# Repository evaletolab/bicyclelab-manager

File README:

# bicyclelab.ORG

Take the control of your electric bicycle. Manage the energy consumtion, wireless I/O with RFM12 or bluetooth, the display, the throttle, the charging, every pieces are open source.

**THIS IS ALPHA SOFTWARE/HARDWARE AND SHOULD BE TREATED ACCORDINGLY.**
**IT IS FUN TO GET RUNNING, BUT EXPECT THINGS TO BE BROKEN.**

##Roadmap
This is a long term project, here is the list of the first ideas: 
* Manage/control your electric bicycle kit with our lithium/electronics/software replacement
* Log data, power, battery voltage, throttle, 
* Use RFM12b as throttle and battery display
* Develop an android application 
* Create the li-ion battery protection module   
* Use the battery for other target with DC 5V 3A output

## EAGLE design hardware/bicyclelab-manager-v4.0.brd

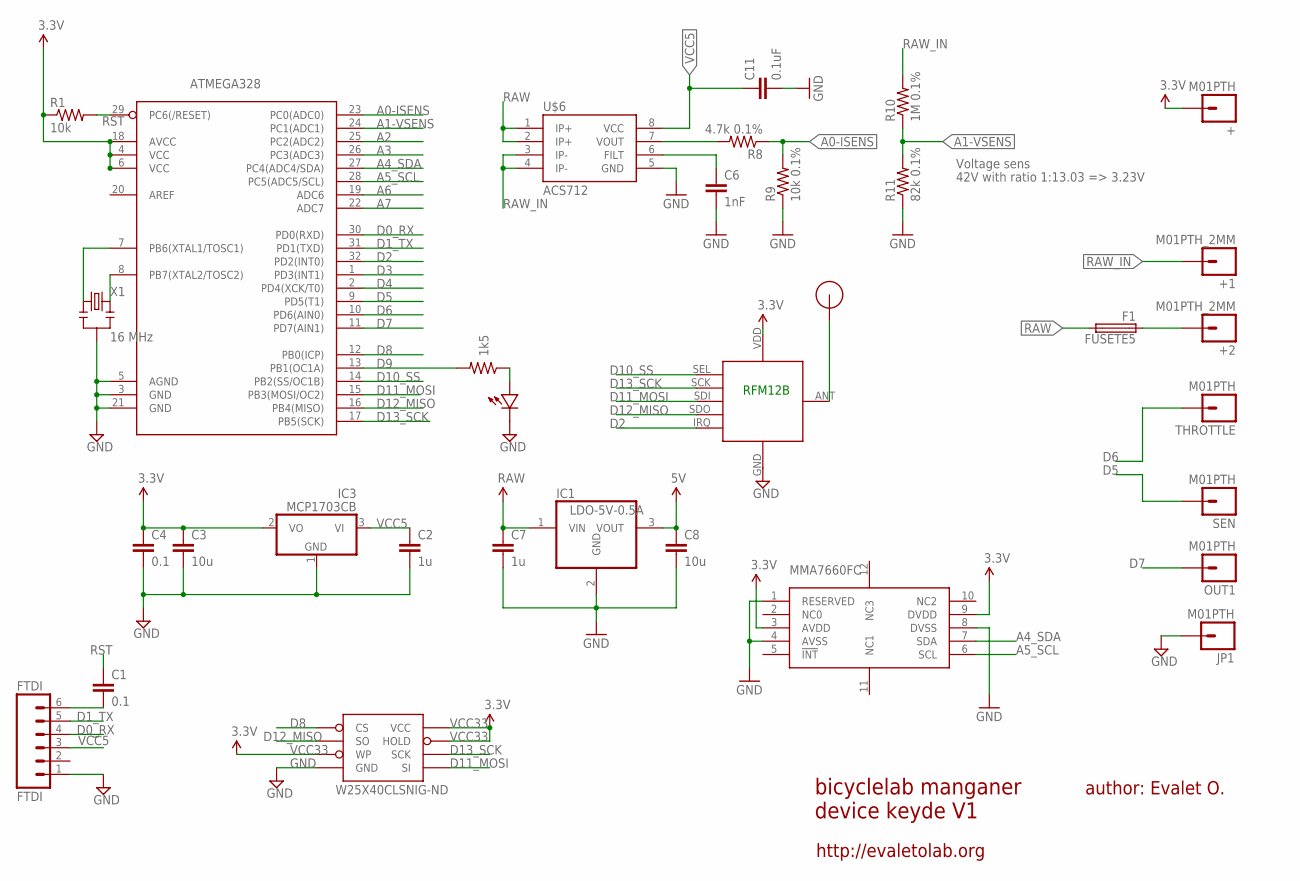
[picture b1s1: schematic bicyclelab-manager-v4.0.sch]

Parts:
+: M01PTH; 1X01
+1, +2: M01PTH_2MM; 1X01_2MM
ATMEGA328: ATMega-328; TQFP32-08
C1, C4: 0.1; 0603-CAP
C2, C7: 1u; 0603-CAP
C3, C8: 10u; 0805-CAP
C6: 1nF; 0805
C11: 0.1uF; 0805
F1: FUSETE5; TE5
FTDI: FTDI; 1X06
IC1: LDO-5V-0.5A; SOT223
IC3: MCP1703CB; SOT23
JP1: M01PTH; 1X01
MMA7660FC: MMA7660FC-DFN10; DFN10
OUT1: M01PTH; 1X01
R1: 10k; 0603-RES
R2: 1k5; 0603-RES
R8: 4.7k 0.1%; 0805
R9: 10k 0.1%; 0805
R10: 1M 0.1%; 0805
R11: 82k 0.1%; 0805
RFM12B: RFM12B_MINPADS; RFM12B-MINPADS
SEN: M01PTH; 1X01
THROTTLE: M01PTH; 1X01
U$1: RFM12B_ANTENNA; RFM12B-ANTENNA
U$2: LED0603; 0603-LED
U$6: ACS712; SO08
W25X40CLSNIG-ND: AT25F512BWIDE_5.3MM; SO08WIDE
X1: 16 MHz; RESONATOR-SMD

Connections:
A0-ISENS: ATMEGA328.23 (PC0(ADC0)), R8.1, R9.2
A1-VSENS: ATMEGA328.24 (PC1(ADC1)), R10.1, R11.2
A2: ATMEGA328.25 (PC2(ADC2))
A3: ATMEGA328.26 (PC3(ADC3))
A4_SDA: ATMEGA328.27 (PC4(ADC4/SDA)), MMA7660FC.7 (SDA)
A5_SCL: ATMEGA328.28 (PC5(ADC5/SCL)), MMA7660FC.6 (SCL)
A6: ATMEGA328.19 (ADC6)
A7: ATMEGA328.22 (ADC7)
D0_RX: ATMEGA328.30 (PD0(RXD)), FTDI.4
D1_TX: ATMEGA328.31 (PD1(TXD)), FTDI.5
D2: ATMEGA328.32 (PD2(INT0)), RFM12B.IRQ
D3: ATMEGA328.1 (PD3(INT1))
D4: ATMEGA328.2 (PD4(XCK/T0))
D5: ATMEGA328.9 (PD5(T1)), SEN.1
D6: ATMEGA328.10 (PD6(AIN0)), THROTTLE.1
D7: ATMEGA328.11 (PD7(AIN1)), OUT1.1
D8: ATMEGA328.12 (PB0(ICP)), W25X40CLSNIG-ND.1 (CS)
D9: ATMEGA328.13 (PB1(OC1A)), R2.2
D10_SS: ATMEGA328.14 (PB2(SS/OC1B)), RFM12B.SEL
D11_MOSI: ATMEGA328.15 (PB3(MOSI/OC2)), RFM12B.SDI (SDI/MOSI), W25X40CLSNIG-ND.5 (SI)
D12_MISO: ATMEGA328.16 (PB4(MISO)), RFM12B.SDO (SDO/MISO), W25X40CLSNIG-ND.2 (SO)
D13_SCK: ATMEGA328.17 (PB5(SCK)), RFM12B.SCK, W25X40CLSNIG-ND.6 (SCK)
GND: ATMEGA328.3 (GND), ATMEGA328.5 (AGND), ATMEGA328.21 (GND), C2.2, C3.2, C4.2, C6.2, C7.2, C8.2, C11.2, FTDI.1, IC1.2 (GND), IC3.1 (GND), JP1.1, MMA7660FC.1 (RESERVED), MMA7660FC.4 (AVSS), MMA7660FC.8 (DVSS), R9.1, R11.1, RFM12B.GND, U$2.MINUS, U$6.5 (GND), W25X40CLSNIG-ND.4 (GND), X1.2
IOUT_: R8.2, U$6.7 (VOUT)
unnamed: ATMEGA328.7 (PB6(XTAL1/TOSC1)), X1.1
unnamed: R2.1, U$2.PLUS
unnamed: RFM12B.ANT, U$1.P$1
unnamed: C6.1, U$6.6 (FILT)
unnamed: C1.2, FTDI.6
unnamed: ATMEGA328.8 (PB7(XTAL2/TOSC2)), X1.3
RAW: C7.1, F1.2, IC1.1 (VIN), U$6.1 (IP+), U$6.2 (IP+)
RAW_IN: +1.1, R10.2, U$6.3 (IP-), U$6.4 (IP-)
RAW_OUT: +2.1, F1.1
RST: ATMEGA328.29 (PC6(/RESET)), C1.1, R1.2
VCC5: C2.1, C8.1, C11.1, FTDI.3, IC1.3 (VOUT), IC3.3 (VI), U$6.8 (VCC)
VCC33: +.1, ATMEGA328.4 (VCC), ATMEGA328.6 (VCC), ATMEGA328.18 (AVCC), C3.1, C4.1, IC3.2 (VO), MMA7660FC.3 (AVDD), MMA7660FC.9 (DVDD), R1.1, RFM12B.VDD, W25X40CLSNIG-ND.3 (WP), W25X40CLSNIG-ND.7 (HOLD), W25X40CLSNIG-ND.8 (VCC)

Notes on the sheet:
bicyclelab manganer device keyde V1
author: Evalet O.
http://evaletolab.org
RFM12B
42V with ratio 1:13.03 => 3.23V
Voltage sens

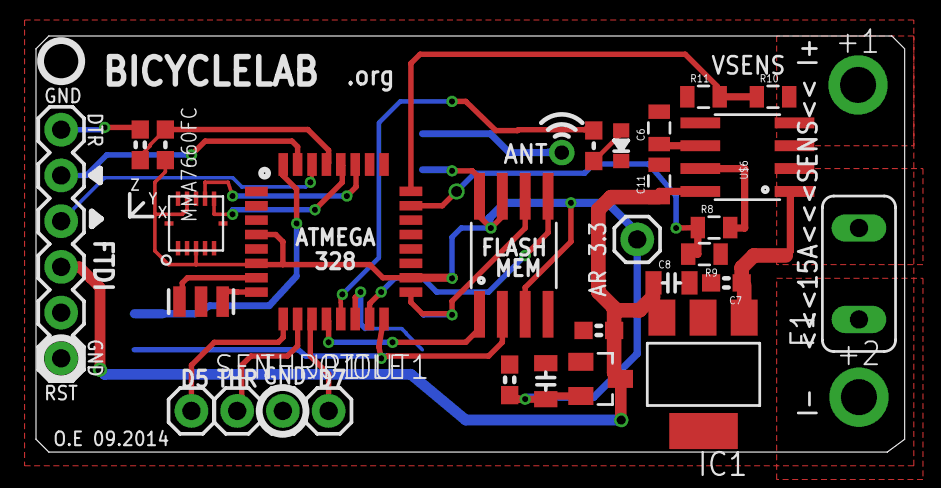
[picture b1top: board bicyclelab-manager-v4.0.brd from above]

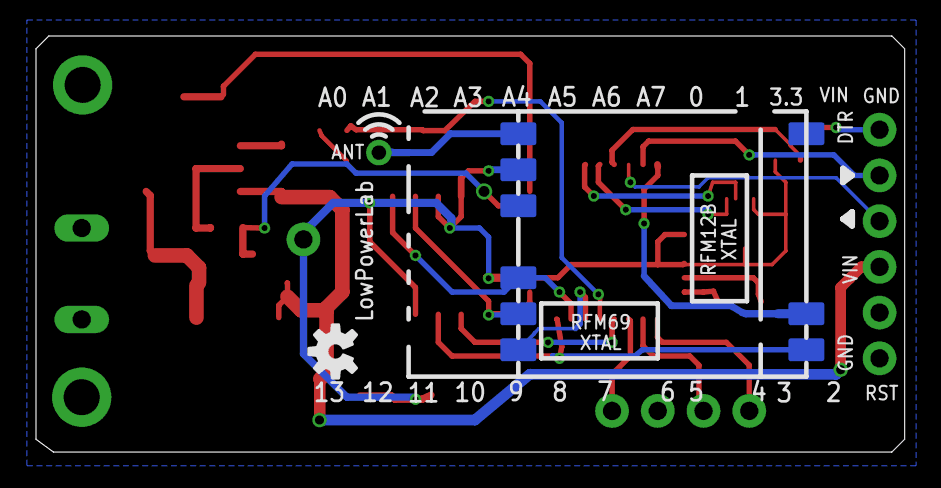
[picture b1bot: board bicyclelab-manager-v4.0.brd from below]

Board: 2 copper layers, 48.3 x 23.1 mm, 34 parts (2 on the bottom side), 30 nets.

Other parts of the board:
U$3: OSHW-LOGO-S

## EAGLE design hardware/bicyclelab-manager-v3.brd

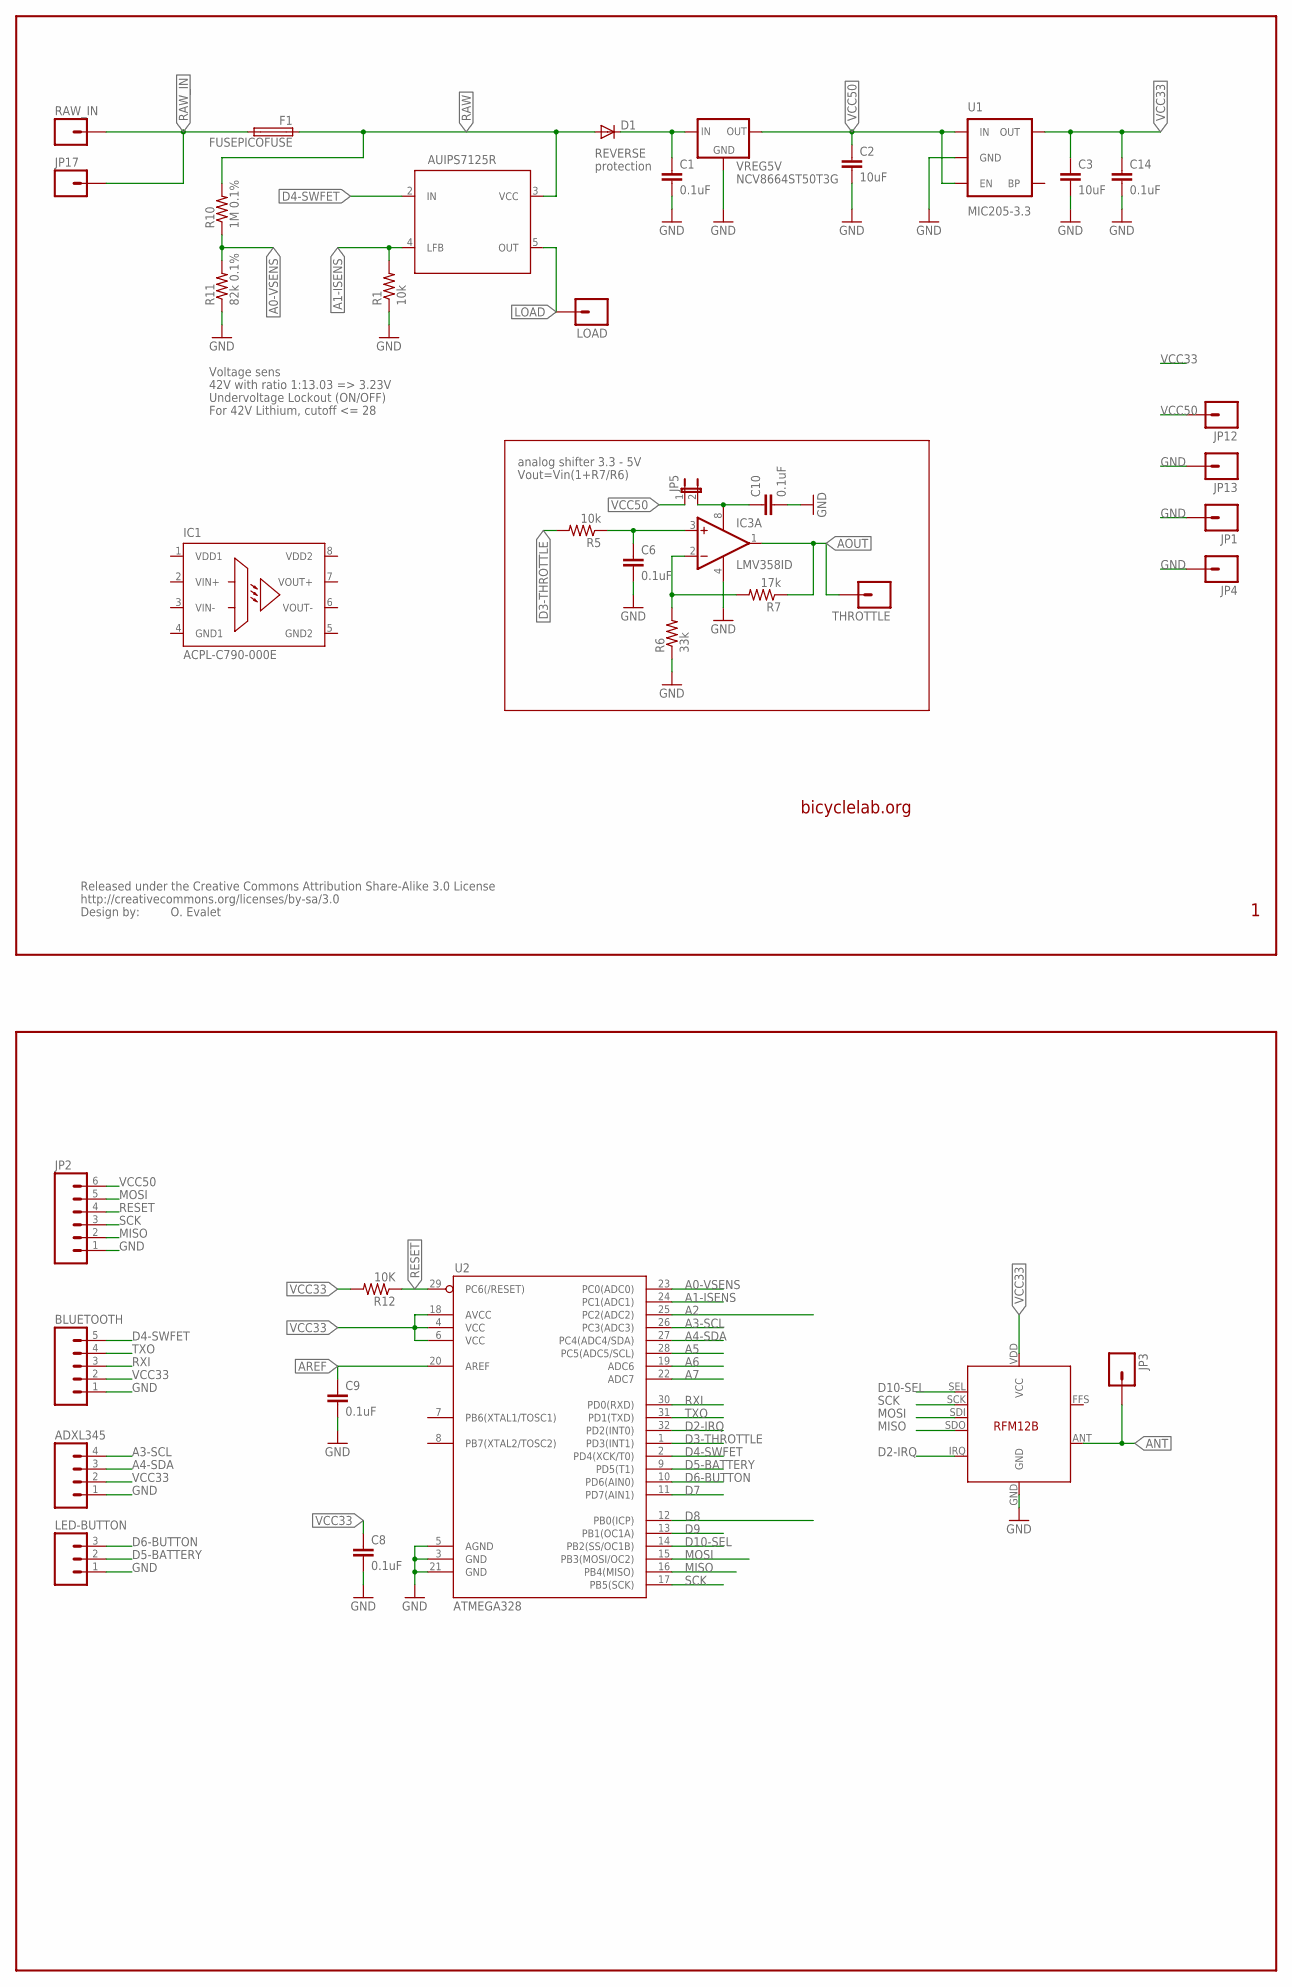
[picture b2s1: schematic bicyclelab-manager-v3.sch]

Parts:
ADXL345: M04PTH; 1X04
BLUETOOTH: M05PTH; 1X05
C1, C6, C10: 0.1uF; 0805
C2, C3: 10uF; 0805
C8, C9, C14: 0.1uF; 0603-CAP
D1: DIODESOD; SOD-323
F1: FUSEPICOFUSE; PICOFUSE
IC1: ACPL-C790-000E; DIP8
IC3: LMV358ID; SO08
JP1, JP4, JP17: M01PTH_2MM; 1X01_2MM
JP2: M06EM406; EM406
JP3: M01SMD-4.5X1.5; PAD-1.5X4.5
JP5: JUMPER-2PTH_LOCK; 1X02_LOCK
JP12, JP13: M01PTH; 1X01
LED-BUTTON: M03PTH; 1X03
LOAD: M01PTH_2MM; 1X01_2MM
R1, R5: 10k; 0805
R6: 33k; 0805
R7: 17k; 0805
R10: 1M 0.1%; 0805
R11: 82k 0.1%; 0805
R12: 10K; 0603-RES
RAW_IN: M01PTH_2MM; 1X01_2MM
THROTTLE: M01PTH; 1X01
U1: MIC205-3.3; SOT23-5
U2: ATMEGA328; TQFP32-08
U$1: RFM12B
U$5: CREATIVE_COMMONS
U$8: AUIPS7125R; DPAK-5
VREG5V: NCV8664ST50T3G; SOT223

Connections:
A0-VSENS: R10.1, R11.2, U2.23 (PC0(ADC0))
A1-ISENS: R1.2, U2.24 (PC1(ADC1)), U$8.4 (LFB)
A2: U2.25 (PC2(ADC2))
A3-SCL: ADXL345.4, U2.26 (PC3(ADC3))
A4-SDA: ADXL345.3, U2.27 (PC4(ADC4/SDA))
A5: U2.28 (PC5(ADC5/SCL))
A6: U2.19 (ADC6)
A7: U2.22 (ADC7)
ANT: JP3.P$1, U$1.ANT
AOUT: IC3.1 (OUT), R7.1, THROTTLE.1
AREF: C9.1, U2.20 (AREF)
D2-IRQ: U2.32 (PD2(INT0)), U$1.IRQ
D3-THROTTLE: R5.2, U2.1 (PD3(INT1))
D4-SWFET: BLUETOOTH.5, U2.2 (PD4(XCK/T0)), U$8.2 (IN)
D5-BATTERY: LED-BUTTON.2, U2.9 (PD5(T1))
D6-BUTTON: LED-BUTTON.3, U2.10 (PD6(AIN0))
D7: U2.11 (PD7(AIN1))
D8: U2.12 (PB0(ICP))
D9: U2.13 (PB1(OC1A))
D10-SEL: U2.14 (PB2(SS/OC1B)), U$1.SEL
GND: ADXL345.1, BLUETOOTH.1, C1.2, C2.2, C3.2, C6.2, C8.2, C9.2, C10.2, C14.2, IC3.4 (V-), JP1.1, JP2.1, JP4.1, JP13.1, LED-BUTTON.1, R1.1, R6.1, R11.1, U1.2 (GND), U2.3 (GND), U2.5 (AGND), U2.21 (GND), U$1.GND, VREG5V.2 (GND)
GND1: IC1.4 (GND1)
GND2: IC1.5 (GND2)
LOAD: LOAD.1, U$8.5 (OUT)
MISO: JP2.2, U2.16 (PB4(MISO)), U$1.SDO
MOSI: JP2.5, U2.15 (PB3(MOSI/OC2)), U$1.SDI
unnamed: C1.1, D1.1 (C), VREG5V.1 (IN)
unnamed: IC3.2 (-IN), R6.2, R7.2
unnamed: C6.1, IC3.3 (+IN), R5.1
RAW: D1.2 (A), F1.1, R10.2, U$8.3 (VCC)
RAW_IN: F1.2, JP17.1, RAW_IN.1
RESET: JP2.4, R12.1, U2.29 (PC6(/RESET))
RXI: BLUETOOTH.3, U2.30 (PD0(RXD))
SCK: JP2.3, U2.17 (PB5(SCK)), U$1.SCK
TXO: BLUETOOTH.4, U2.31 (PD1(TXD))
VCC33: ADXL345.2, BLUETOOTH.2, C3.1, C8.1, C14.1, R12.2, U1.5 (OUT), U2.4 (VCC), U2.6 (VCC), U2.18 (AVCC), U$1.VDD (VCC)
VCC50: C2.1, JP2.6, JP5.1, JP12.1, U1.1 (IN), U1.3 (EN), VREG5V.3 (OUT)
VCC50_: C10.1, IC3.8 (V+), JP5.2
VDD1: IC1.1 (VDD1)
VDD2: IC1.8 (VDD2)
VIN+: IC1.2 (VIN+)
VIN-: IC1.3 (VIN-)
VOUT+: IC1.7 (VOUT+)
VOUT-: IC1.6 (VOUT-)

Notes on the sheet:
bicyclelab.org
O. Evalet
Undervoltage Lockout (ON/OFF)
For 42V Lithium, cutoff <= 28
42V with ratio 1:13.03 => 3.23V
Voltage sens
analog shifter 3.3 - 5V
Vout=Vin(1+R7/R6)
REVERSE
protection

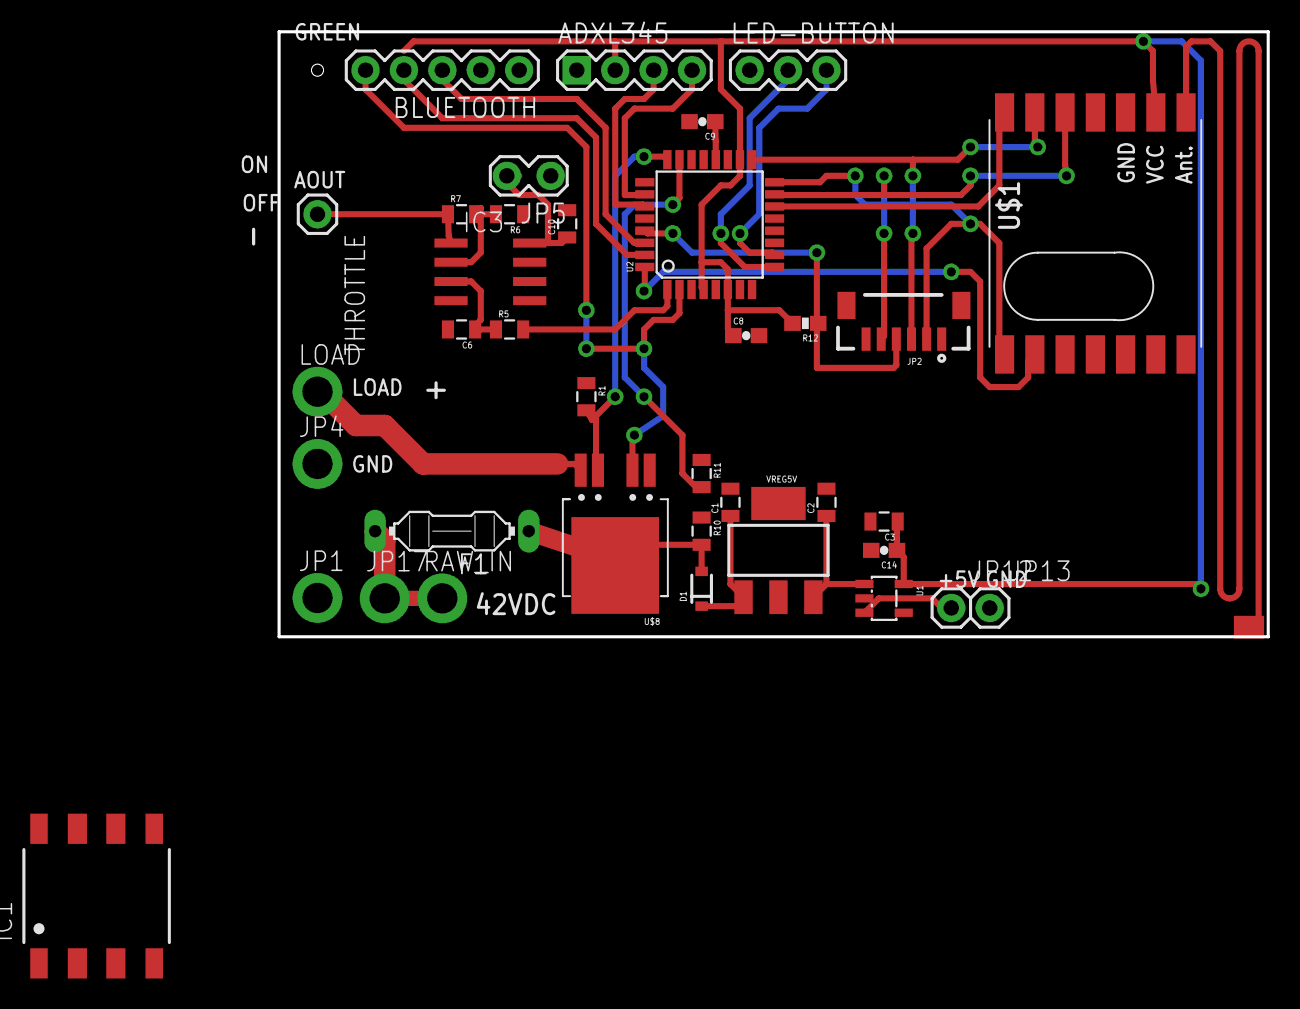
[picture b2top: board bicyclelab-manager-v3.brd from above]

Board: 2 copper layers, 65.4 x 40.0 mm, 39 parts (0 on the bottom side), 29 nets.

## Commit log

2012-02-09 README
2012-10-07 new release
2012-10-07 new datasheet
2012-10-07 Create gh-pages branch via GitHub
2015-06-26 new release based on monteino hardware
2015-06-26 new pcb picture
2015-06-26 initial doc

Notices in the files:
parts and their libraries:
SparkFun: Released under the Creative Commons Attribution Share-Alike 3.0 License
SparkFun: http://creativecommons.org/licenses/by-sa/3.0
SparkFun-Connectors: Licensing: CC v3.0 Share-Alike You are welcome to use this library for commercial purposes.
